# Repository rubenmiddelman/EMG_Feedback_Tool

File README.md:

# EMG Feedback tool
This Repo is for the Quest project at the HU university of applied siences

In this project the goals is to make a tool that uses EMG Measurments to give feedback to the user.
This is done so the user learns to relax the muscles more.

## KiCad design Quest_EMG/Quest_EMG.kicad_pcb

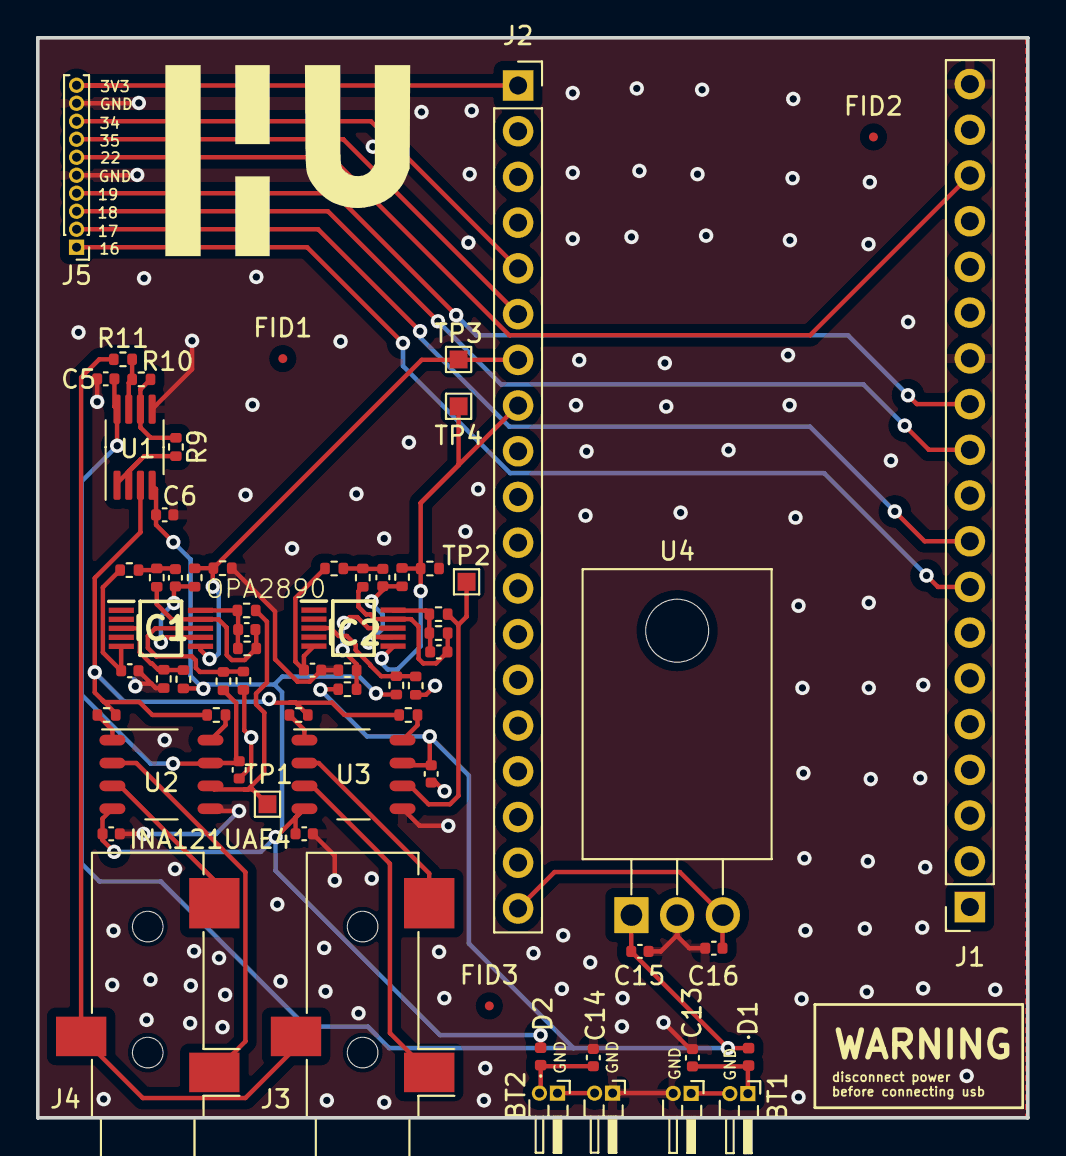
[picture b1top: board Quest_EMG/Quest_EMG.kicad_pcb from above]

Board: 2 copper layers, 55.0 x 60.0 mm, 67 parts (0 on the bottom side), 47 nets.

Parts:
BT1, BT2, BT3, BT4: Battery_Cell; PinHeader_1x02_P1.00mm_Horizontal
C1, C2, C3, C4: 100n; C_0402_1005Metric
C5, C6: C; C_0402_1005Metric
C7, C8, C9, C10, C11, C12: 390n; C_0402_1005Metric
C13, C14: 10n; C_0402_1005Metric
C15: 10uF; C_0402_1005Metric
C16: 100nF; C_0402_1005Metric
D1, D2: D_Schottky; D_0402_1005Metric
FID1, FID2, FID3: Fiducial; Fiducial_0.5mm_Mask1.5mm
IC1, IC2: OPA2890IDGST; SOP50P490X110-10N
J1, J2: Conn_01x19_Socket; PinSocket_1x19_P2.54mm_Vertical
J3, J4: AudioJack3; Jack_3.5mm_CUI_SJ-3523-SMT_Horizontal
J5: Conn_01x10_Pin; PinHeader_1x10_P1.00mm_Vertical
R1, R4, R5, R8: 100; R_0402_1005Metric
R9: 10K; R_0402_1005Metric
R10: 390K; R_0402_1005Metric
R11: 390k; R_0402_1005Metric
R12, R13, R26, R28: 33k; R_0402_1005Metric
R14, R15, R30, R31: 56k; R_0402_1005Metric
R16, R17, R18, R19, R20, R21, R22, R23, R27, R29: 10k; R_0402_1005Metric
R24, R25: 5k8; R_0402_1005Metric
TP1, TP2, TP3, TP4: TestPoint; TestPoint_Pad_1.0x1.0mm
U1: AD8620; MSOP-8_3x3mm_P0.65mm
U2, U3: INA121UAE4
U4: L7805; TO-220F-3_Horizontal_TabDown

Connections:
32: IC1.6 (-IN_B), J2.7, R24.2, R27.1, TP3.1
33: IC2.6 (-IN_B), J2.8, R25.2, R29.1, TP4.1
+5V: C16.1, J2.19, U4.3 (OUT)
+9V: C1.2, C3.2, C5.1, C15.1, D1.1 (K), R26.1, R28.1, U1.8 (V+), U2.7 (V+), U3.7 (V+), U4.1 (IN)
-9V: C2.1, C4.1, C6.1, D2.2 (A), R12.1, R13.1, U1.4 (V-), U2.4 (V-), U3.4 (V-)
/Bluetooth ESP/3V3: J2.1, J5.10
/Bluetooth ESP/16: J1.8, J5.1
/Bluetooth ESP/17: J1.9, J5.2
/Bluetooth ESP/18: J1.11, J5.3
/Bluetooth ESP/19: J1.12, J5.4
/Bluetooth ESP/22: J1.17, J5.6
/Bluetooth ESP/34: J2.5, J5.8
/Bluetooth ESP/35: J2.6, J5.7
/Connector Opamp/IN1.1: J4.S, U2.2 (IN-)
/Connector Opamp/IN1.2: J3.S, U3.3 (IN+)
/Connector Opamp/IN2.1: J4.T, U2.3 (IN+)
/Connector Opamp/IN2.2: J3.T, U3.2 (IN-)
/Connector Opamp/Right_Leg: J3.R, J4.R, R11.1
GND: BT1.1 (+), BT3.2 (-), C1.1, C2.2, C3.1, C4.2, C5.2, C6.2, C7.2, C8.2, C13.2, C14.2, C15.2, C16.2, J1.13, J1.19, J5.5, J5.9, R14.2, R15.2, R27.2, R29.2, R30.2, R31.2, U1.5 (+), U2.5 (REF), U3.5 (REF), U4.2 (GND)
In_amp1: R18.2, TP1.1, U2.6 (OUT)
In_amp2: R19.2, TP2.1, U3.6 (OUT)
unnamed: BT1.2 (-), BT4.1 (+)
unnamed: BT2.1 (+), C13.1, D1.2 (A)
unnamed: BT2.2 (-), BT3.1 (+)
unnamed: BT4.2 (-), C14.1, D2.1 (K)
unnamed: C9.2, R16.1, R20.2
unnamed: C10.2, R17.1, R21.2
unnamed: C7.1, IC1.5 (+IN_B), R16.2
unnamed: IC1.8 (+VS), R26.2, R30.1
unnamed: C11.1, IC1.10 (-IN_A), R18.1, R22.2
unnamed: IC1.3 (-VS), R12.2, R14.1
unnamed: C11.2, IC1.9 (OUT_A), R20.1, R22.1
unnamed: C9.1, IC1.7 (OUT_B), R24.1
unnamed: C8.1, IC2.5 (+IN_B), R17.2
unnamed: IC2.8 (+VS), R28.2, R31.1
unnamed: C12.1, IC2.10 (-IN_A), R19.1, R23.2
unnamed: IC2.3 (-VS), R13.2, R15.1
unnamed: C12.2, IC2.9 (OUT_A), R21.1, R23.1
unnamed: C10.1, IC2.7 (OUT_B), R25.1
unnamed: R1.1, U2.1 (RG)
unnamed: R4.2, U2.8 (RG)
unnamed: R5.1, U3.1 (RG)
unnamed: R8.2, U3.8 (RG)
unnamed: R10.1, R11.2, U1.7
unnamed: R9.2, U1.1, U1.2 (-)
unnamed: R9.1, R10.2, U1.6 (-)
RL_conn: R1.2, R4.1, R5.2, R8.1, U1.3 (+)

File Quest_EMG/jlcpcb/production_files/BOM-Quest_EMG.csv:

Comment,Designator,Footprint,LCSC
Fiducial,FID1,Fiducial_0.5mm_Mask1.5mm,
10K,R9,R_0402_1005Metric,
INA121UAE4,U2,INA121UAE4,
D_Schottky,D2,D_0402_1005Metric,
390k,R11,R_0402_1005Metric,
390n,C12,C_0402_1005Metric,
AD8620,U1,MSOP-8_3x3mm_P0.65mm,
390n,C7,C_0402_1005Metric,
Conn_01x19_Socket,J1,PinSocket_1x19_P2.54mm_Vertical,
5k8,R25,R_0402_1005Metric,
56k,R31,R_0402_1005Metric,
10n,C14,C_0402_1005Metric,
OPA2890IDGST,IC1,SOP50P490X110-10N,
390K,R10,R_0402_1005Metric,
390n,C11,C_0402_1005Metric,
10k,R16,R_0402_1005Metric,
33k,R12,R_0402_1005Metric,
L7805,U4,TO-220F-3_Horizontal_TabDown,
AudioJack3,J3,Jack_3.5mm_CUI_SJ-3523-SMT_Horizontal,
56k,R15,R_0402_1005Metric,
56k,R14,R_0402_1005Metric,
100nF,C16,C_0402_1005Metric,
100n,C4,C_0402_1005Metric,
100,R8,R_0402_1005Metric,
33k,R13,R_0402_1005Metric,
Battery_Cell,BT2,PinHeader_1x02_P1.00mm_Horizontal,
5k8,R24,R_0402_1005Metric,
33k,R28,R_0402_1005Metric,
Battery_Cell,BT3,PinHeader_1x02_P1.00mm_Horizontal,
C,C5,C_0402_1005Metric,
TestPoint,TP2,TestPoint_Pad_1.0x1.0mm,
Conn_01x10_Pin,J5,PinHeader_1x10_P1.00mm_Vertical,
Fiducial,FID2,Fiducial_0.5mm_Mask1.5mm,
10k,R23,R_0402_1005Metric,
Conn_01x19_Socket,J2,PinSocket_1x19_P2.54mm_Vertical,
100,R5,R_0402_1005Metric,
100n,C2,C_0402_1005Metric,
10k,R29,R_0402_1005Metric,
100,R4,R_0402_1005Metric,
10k,R17,R_0402_1005Metric,
390n,C8,C_0402_1005Metric,
10k,R19,R_0402_1005Metric,
56k,R30,R_0402_1005Metric,
INA121UAE4,U3,INA121UAE4,
OPA2890IDGST,IC2,SOP50P490X110-10N,
Battery_Cell,BT1,PinHeader_1x02_P1.00mm_Horizontal,
Battery_Cell,BT4,PinHeader_1x02_P1.00mm_Horizontal,
TestPoint,TP3,TestPoint_Pad_1.0x1.0mm,
10k,R21,R_0402_1005Metric,
10k,R22,R_0402_1005Metric,
10k,R27,R_0402_1005Metric,
33k,R26,R_0402_1005Metric,
100n,C1,C_0402_1005Metric,
D_Schottky,D1,D_0402_1005Metric,
10k,R18,R_0402_1005Metric,
TestPoint,TP1,TestPoint_Pad_1.0x1.0mm,
C,C6,C_0402_1005Metric,
10n,C13,C_0402_1005Metric,
10uF,C15,C_0402_1005Metric,
AudioJack3,J4,Jack_3.5mm_CUI_SJ-3523-SMT_Horizontal,
TestPoint,TP4,TestPoint_Pad_1.0x1.0mm,
100n,C3,C_0402_1005Metric,
Fiducial,FID3,Fiducial_0.5mm_Mask1.5mm,
390n,C9,C_0402_1005Metric,
390n,C10,C_0402_1005Metric,
10k,R20,R_0402_1005Metric,
100,R1,R_0402_1005Metric,

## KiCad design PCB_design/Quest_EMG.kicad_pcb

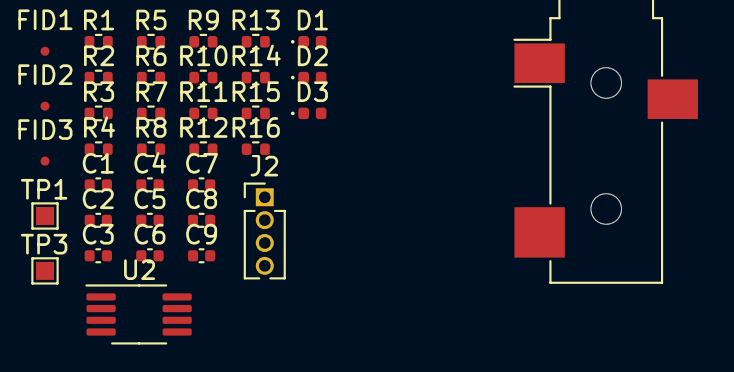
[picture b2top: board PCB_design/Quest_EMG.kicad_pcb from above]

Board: 2 copper layers, 36 parts (0 on the bottom side), 21 nets, no tracks yet.

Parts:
C1, C2: 10n; C_0402_1005Metric
C3, C4: 100n; C_0402_1005Metric
C5, C6: C; C_0402_1005Metric
C7, C8, C9: 390n; C_0402_1005Metric
D1, D2: D_Schottky; D_0402_1005Metric
D3: LED; LED_0402_1005Metric
FID1, FID2, FID3: Fiducial; Fiducial_0.5mm_Mask1.5mm
J1: AudioJack2_Ground; Jack_3.5mm_CUI_SJ-3523-SMT_Horizontal
J2: Conn_01x04_Pin; PinHeader_1x04_P1.27mm_Vertical
R1, R3: 390; R_0402_1005Metric
R2, R4: 15; R_0402_1005Metric
R5: 470; R_0402_1005Metric
R6, R8, R10, R11, R12, R15: 10k; R_0402_1005Metric
R7: 2k; R_0402_1005Metric
R9: 10K; R_0402_1005Metric
R13: 390K; R_0402_1005Metric
R14: 5k8; R_0402_1005Metric
R16: 390k; R_0402_1005Metric
TP1, TP3: TestPoint; TestPoint_Pad_1.0x1.0mm
U2: AD8620; MSOP-8_3x3mm_P0.65mm

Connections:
+9V: C3.2, C5.1, D2.1 (K), U2.8 (V+)
-9V: C4.1, C6.1, D1.2 (A), U2.4 (V-)
Cable_Ground: J2.1, R9.2, U2.1, U2.2 (-)
GND: C1.2, C2.2, C3.1, C4.2, C5.2, C6.2, C7.2, D3.1 (K), R7.2, R15.2, U2.5 (+)
In_amp: R10.2, TP1.1
unnamed: C2.1, D2.2 (A)
unnamed: C1.1, D1.1 (K)
unnamed: C8.2, R8.1, R11.2
unnamed: D3.2 (A), R5.2
unnamed: R6.2, R7.1
unnamed: C7.1, R8.2
unnamed: C9.1, R10.1, R12.2
unnamed: C9.2, R11.1, R12.1
unnamed: C8.1, R14.1
unnamed: R1.2, R2.1
unnamed: R3.2, R4.1
unnamed: R13.1, R16.2, U2.7
unnamed: R9.1, R13.2, U2.6 (-)
OPAMP_Output: R14.2, R15.1, TP3.1
RL_conn: R2.2, R3.1, U2.3 (+)
Right_Leg: J2.2, R16.1

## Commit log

2023-02-14 "README initial commit"
2023-02-20 Holla Rubeno
    yo soy Jonas pero no hablo Holandais.
    tiene un higo the burro
2023-04-03 schema pcb design
2023-04-03 cleanup crew has arrived
2023-05-22 pcb upload
    hier is de pcb jongu
2023-05-22 oopsie
2023-05-22 To Do list update:
    this is the starting point of the PCB updates
2023-05-22 cleanup
2023-05-22 62 times amplification
2023-05-22 feature amplification
2023-05-22 forgot something
2023-06-02 Revert "Create Quest_EMG-2023-05-22_162835.zip"
    This reverts commit dac368ae62c13921a57f645220ca74b657ad002b.
2023-06-30 adds final version of PCB
